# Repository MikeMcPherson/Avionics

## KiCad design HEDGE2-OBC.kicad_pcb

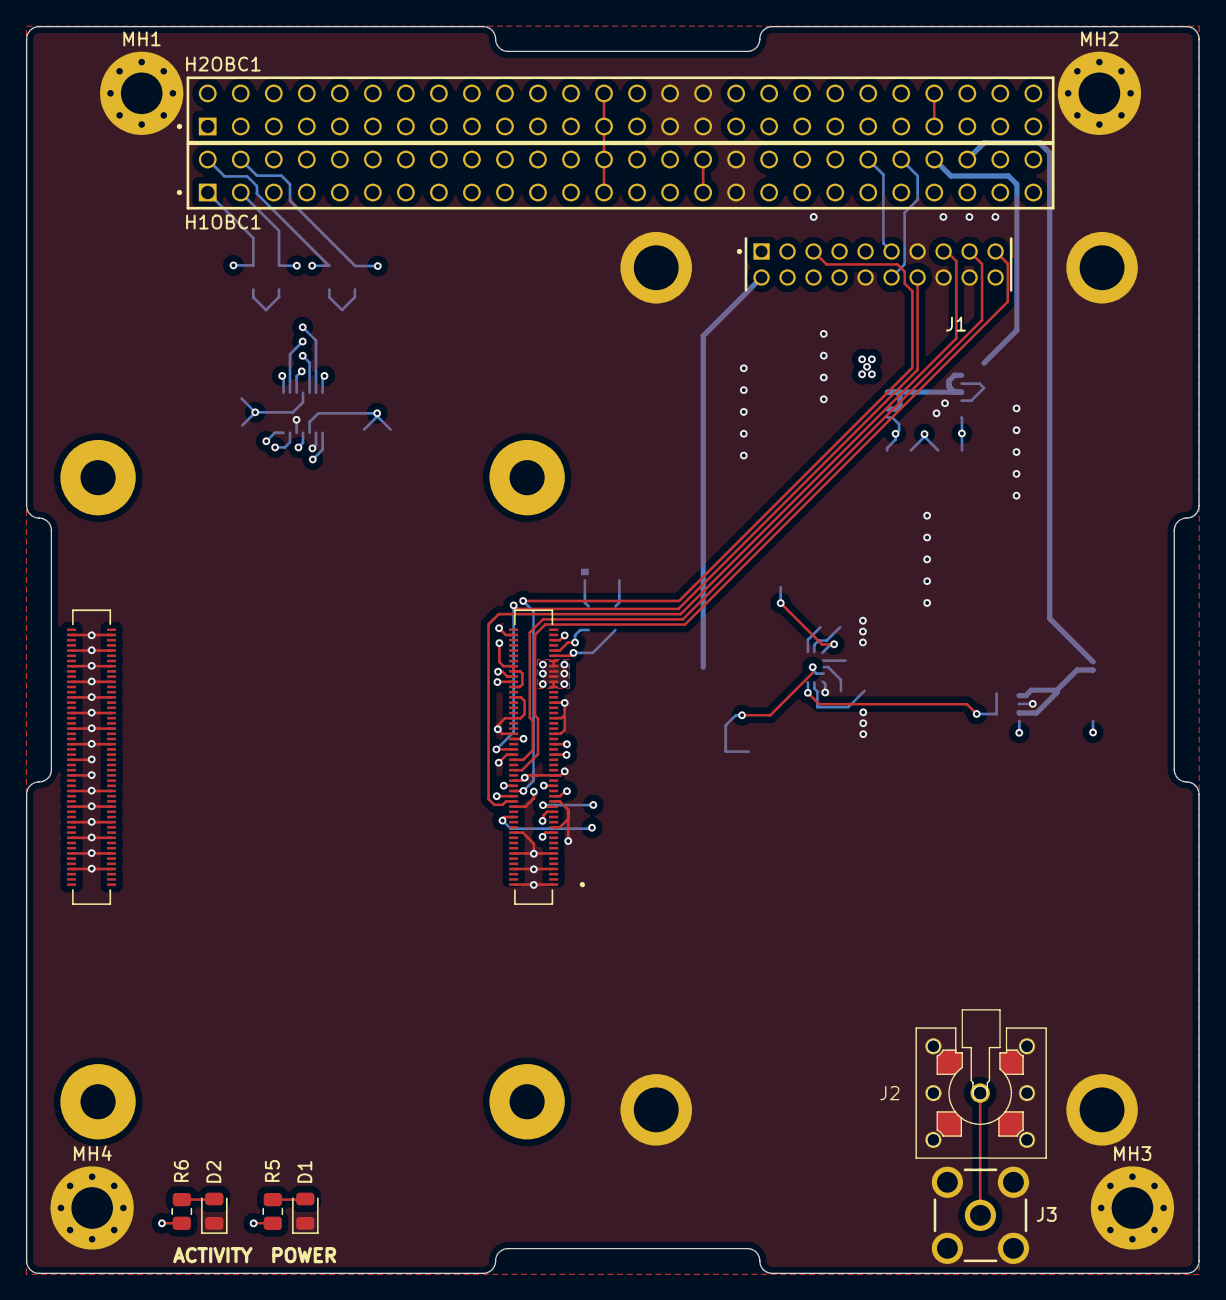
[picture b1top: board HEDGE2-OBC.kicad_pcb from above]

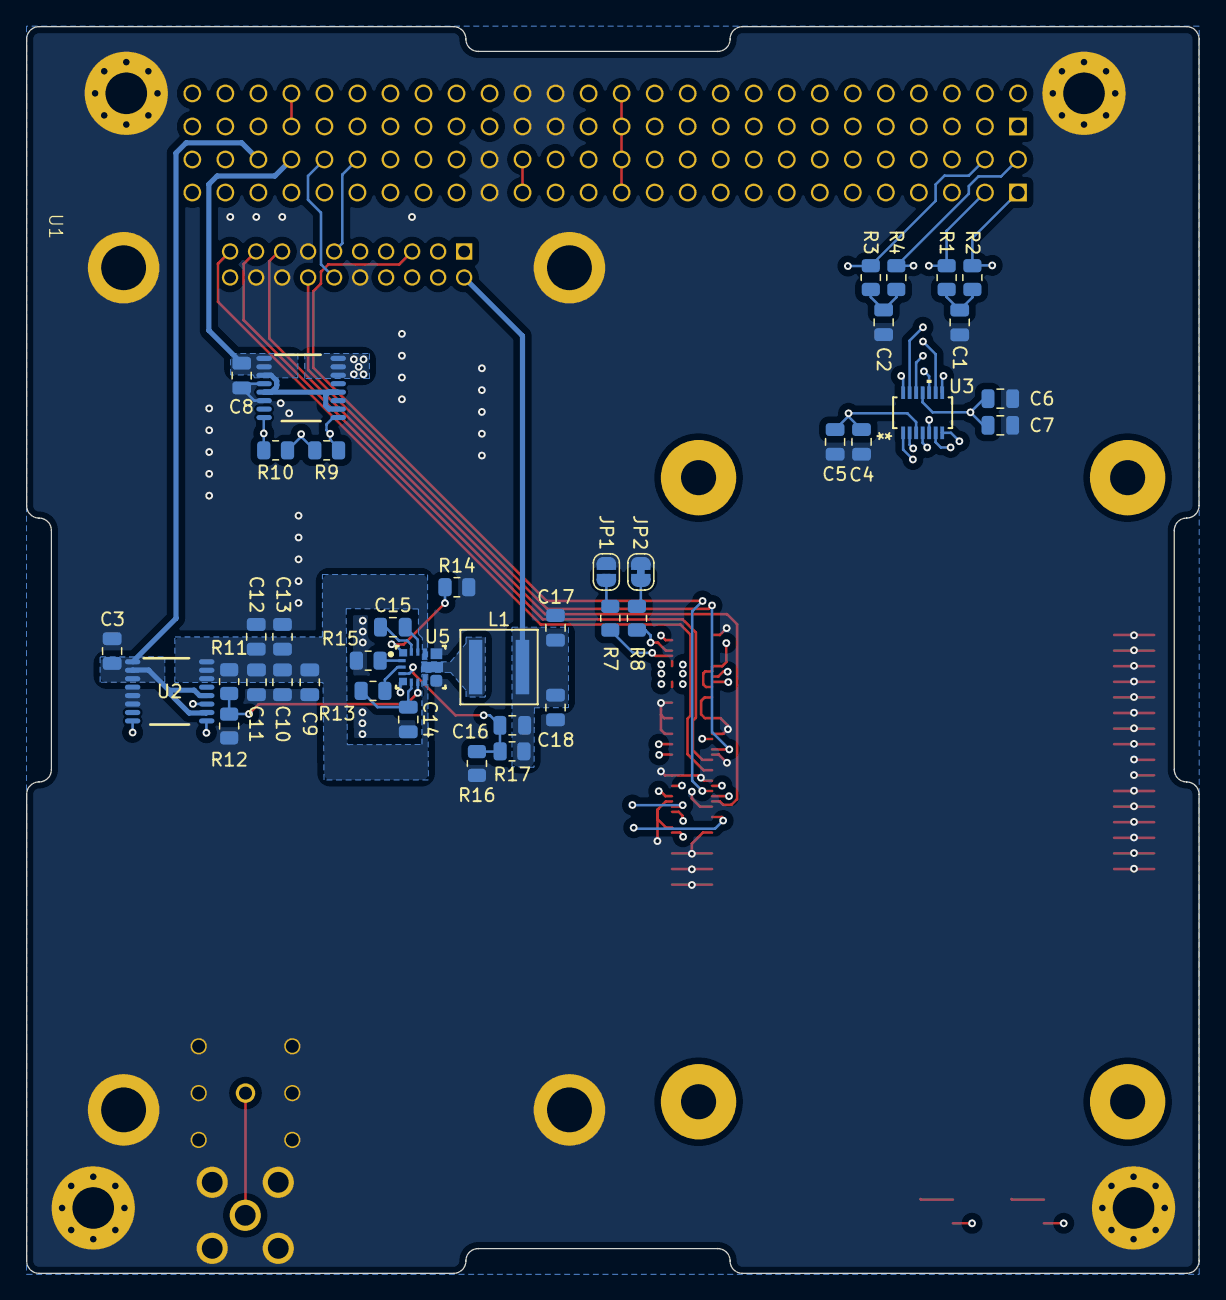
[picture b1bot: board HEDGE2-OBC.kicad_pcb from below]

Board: 4 copper layers, 90.2 x 95.9 mm, 55 parts (41 on the bottom side), 53 nets.

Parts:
C1, C2, C5, C7: 0u1; C_0805_2012Metric
C3, C8: 0.1u; C_0805_2012Metric
C4, C6: 4u7; C_0805_2012Metric
C9: 100u, 35V; C_0805_2012Metric
C10, C11: 10u, 25V, 0805; C_0805_2012Metric
C12, C13: 0u1, 50v, 0805; C_0805_2012Metric
C14: 2u2, 10V, 0805; C_0805_2012Metric
C15: 0u1, 50V, 0805; C_0805_2012Metric
C16: 33p; C_0805_2012Metric
C17, C18: 47u, 10V, 0805; C_0805_2012Metric
D1: LED GREEN; LED_0805_2012Metric
D2: LED RED; LED_0805_2012Metric
H1OBC1, H2OBC1: Conn_02x26_Odd_Even; SAMTEC_ESQ-126-39-G-D
J1: SQT-110-01-L-D; SAMTEC_SQT-110-01-L-D
J2: MMBX-S50-0-18
J3: SMA-J-P-X-RA-TH1; SAMTEC_SMA-J-P-X-RA-TH1
JP1: WiFi_nDisable; SolderJumper-2_P1.3mm_Open_RoundedPad1.0x1.5mm
JP2: BT_nDisable; SolderJumper-2_P1.3mm_Bridged_RoundedPad1.0x1.5mm
L1: XGL5050-182MEC; IND_XGL5050_COC
MH1, MH2, MH3, MH4: MountingHole_Pad; MountingHole_3.2mm_M3_Pad_Via
Module1: ComputeModule4; MODULE_CM4102008
R1, R2, R3, R4: 60; R_0805_2012Metric
R5: 39; R_0805_2012Metric
R6: 45; R_0805_2012Metric
R7, R8: 1k; R_0805_2012Metric
R9, R10: 4k7; R_0805_2012Metric
R11: 16k9; R_0805_2012Metric
R12: 6k04; R_0805_2012Metric
R13: 11k3; R_0805_2012Metric
R14: 11k8; R_0805_2012Metric
R15: 10k; R_0805_2012Metric
R16: 4k99; R_0805_2012Metric
R17: 28k; R_0805_2012Metric
U1: OEM719
U2, U4: INA260AIPWR; PW0016A_L
U3: TCAN1046AVDYYRQ1; SOT23_DYY_TEX
U5: TPS543320RPYR; RPY0014A-MFG

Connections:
+3V3: C4.1, C5.1, Module1.78 (GPIO_VREF(1.8v/3.3v_Input)), Module1.84 (+3.3v_(Output)), Module1.86 (+3.3v_(Output)), R9.2, R10.2, U3.3 (VCC)
+5V_CM4: C6.1, C7.1, Module1.77 (+5v_(Input)), Module1.79 (+5v_(Input)), Module1.81 (+5v_(Input)), Module1.83 (+5v_(Input)), Module1.85 (+5v_(Input)), Module1.87 (+5v_(Input)), U3.11 (VIO), U4.14 (IN-), U4.15 (IN-), U4.16 (IN-)
+5V_GNSS: C3.2, H1OBC1.48, U2.1 (IN+), U2.2 (IN+), U2.3 (IN+), U2.10 (VS), U2.12 (VBUS)
+5V_MPU: C8.2, H1OBC1.46, U4.1 (IN+), U4.2 (IN+), U4.3 (IN+), U4.5 (A0), U4.10 (VS), U4.12 (VBUS)
+5V_OEM719B: C16.1, C17.1, C18.1, J1.02, L1.2, R17.2
/OBC/5V_PERM: H1OBC1.25, H1OBC1.26, H2OBC1.25, H2OBC1.26
/OBC/BATT: H2OBC1.45, H2OBC1.46
/OBC/CAN_A_H: H1OBC1.03, R1.1, U3.13 (CANH1)
/OBC/CAN_A_L: H1OBC1.01, R2.2, U3.12 (CANL1)
/OBC/CAN_A_RXD: Module1.51 (GPIO15), U3.4 (RXD1)
/OBC/CAN_A_S: Module1.29 (GPIO16), U3.14 (STB1)
/OBC/CAN_A_TXD: Module1.55 (GPIO14), U3.1 (TXD1)
/OBC/CAN_B_H: H1OBC1.04, R3.1, U3.10 (CANH2)
/OBC/CAN_B_L: H1OBC1.02, R4.2, U3.9 (CANL2)
/OBC/CAN_B_RXD: Module1.35 (ID_SC), U3.7 (RXD2)
/OBC/CAN_B_S: Module1.58 (GPIO2), U3.8 (STB2/NSTB2)
/OBC/CAN_B_TXD: Module1.36 (ID_SD), U3.6 (TXD2)
/OBC/CHARGE: H1OBC1.31, H1OBC1.32
/OBC/GNSS_NRESET_IN: J1.05, Module1.38 (GPIO11)
/OBC/GNSS_PPS: J1.19, Module1.46 (GPIO22)
/OBC/GNSS_PV: J1.17, Module1.50 (GPIO17)
/OBC/GNSS_RXD1: H1OBC1.44, J1.12
/OBC/GNSS_RXD2: J1.15, Module1.34 (GPIO5)
/OBC/GNSS_TXD1: H1OBC1.42, J1.11
/OBC/GNSS_TXD2: J1.14, Module1.54 (GPIO4)
/OBC/INA260_OEM719/LOAD: C9.1, C10.1, C11.1, C12.1, C13.1, R11.1, U2.14 (IN-), U2.15 (IN-), U2.16 (IN-), U5.8 (VIN), U5.12 (VIN)
/OBC/PI_nLED_Activity: Module1.21 (PI_nLED_Activity), R5.1
/OBC/RF_GNSS: J2.1 (In), J3.1
/OBC/SCL0: Module1.80 (SCL0), R9.1, U2.9 (SCL), U4.9 (SCL)
/OBC/SDA0: Module1.82 (SDA0), R10.1, U2.8 (SDA), U4.8 (SDA)
/OBC/UART_COMM_RX: H1OBC1.24, Module1.40 (GPIO9)
/OBC/UART_COMM_TX: H1OBC1.22, Module1.39 (GPIO8)
/OBC/UART_DATA_RX: H1OBC1.40, Module1.28 (GPIO13)
/OBC/UART_DATA_TX: H1OBC1.38, Module1.31 (GPIO12)
/OBC/nPWR_LED: Module1.95 (nPI_LED_PWR), R6.1
GND: C1.2, C2.2, C3.1, C4.2, C5.2, C6.2, C7.2, C8.1, C9.2, C10.2, C11.2, C12.2, C13.2, C14.2, C17.2, C18.2, D1.1 (K), D2.1 (K), H1OBC1.33, H1OBC1.34, H2OBC1.29, H2OBC1.30, H2OBC1.31, H2OBC1.32, J1.10, J1.13, J1.16, J1.18, J2.2 (Ext), J3.2, J3.3, J3.4, J3.5, JP1.1 (A), JP2.2 (B), MH1.1, MH2.1, MH3.1, MH4.1, Module1.1 (GND), Module1.2 (GND), Module1.7 (GND), Module1.8 (GND), Module1.13 (GND), Module1.14 (GND), Module1.22 (GND), Module1.23 (GND), Module1.32 (GND), Module1.33 (GND), Module1.42 (GND), Module1.43 (GND), Module1.52 (GND), Module1.53 (GND), Module1.59 (GND), Module1.60 (GND), Module1.65 (GND), Module1.66 (GND), Module1.71 (GND), Module1.74 (GND), Module1.98 (GND), Module1.107 (GND), Module1.108 (GND), Module1.113 (GND), Module1.114 (GND), Module1.119 (GND), Module1.120 (GND), Module1.125 (GND), Module1.126 (GND), Module1.131 (GND), Module1.132 (GND), Module1.137 (GND), Module1.138 (GND), Module1.144 (GND), Module1.150 (GND), Module1.155 (GND), Module1.156 (GND), Module1.161 (GND), Module1.162 (GND), Module1.167 (GND), Module1.168 (GND), Module1.173 (GND), Module1.174 (GND), Module1.179 (GND), Module1.180 (GND), Module1.185 (GND), Module1.186 (GND), Module1.191 (GND), Module1.192 (GND), Module1.197 (GND), Module1.198 (GND), R12.2, R13.2, R14.2, R16.1, U1.22 (GND), U1.23 (GND), U1.24 (GND), U1.25 (GND), U2.4 (A1), U2.5 (A0), U2.6 (GND), U2.11 (GND), U3.2 (GND1), U3.5 (GND2), U4.4 (A1), U4.6 (GND), U4.11 (GND), U5.5 (AGND), U5.9 (PGND), U5.11 (PGND)
unnamed: C1.1, R1.2, R2.1
unnamed: C2.1, R3.2, R4.1
unnamed: C15.2, U5.13 (SW)
unnamed: D1.2 (A), R5.2
unnamed: D2.2 (A), R6.2
unnamed: JP1.2 (B), R7.1
unnamed: JP2.1 (A), R8.2
unnamed: L1.1, U5.10 (SW)
unnamed: Module1.91 (BT_nDisable), R8.1
unnamed: Module1.89 (WiFi_nDisable), R7.2
unnamed: C15.1, U5.14 (BOOT)
unnamed: C14.1, R15.1, U5.6 (BP5)
unnamed: R11.2, R12.1, U5.7 (EN)
unnamed: C16.2, R16.2, R17.1, U5.4 (FB)
unnamed: R13.1, U5.2 (MODE)
unnamed: R15.2, U5.3 (PGOOD)
unnamed: R14.1, U5.1 (SYNC_FSEL)

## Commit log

2025-06-27 Initial setup; copy from HEDGE1
2025-06-30 Initial schematic entry
2025-07-03 OBC: initialize schematic, spacecraft bus
2025-07-03 OBC: schematic input
2025-07-03 OBC: initial schematic entry complete
2025-07-06 OBC: preliminary layout
2025-07-26 OBC: start PCB layout
2025-07-27 OBC: Continue PCB lauout
2025-07-27 Continue PCB layout
2025-08-01 OBC: complete layout first pass
2025-08-18 Layout confirmed, PCBs ordered
2025-09-07 Separate PCBs into individual repos to allow for multiple workgroups
2025-09-09 Cleanup after splitting PCBs into separate repos
2025-09-09 Add RS-485 interfaces; modify for 5V power input
